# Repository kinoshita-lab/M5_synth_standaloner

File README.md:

# M5 Synth standaloner san

M5 Synth standaloner san is a handy PCB which enables standalone use of:
- Unit Synth https://docs.m5stack.com/ja/unit/Unit-Synth 
- Unit MIDI https://docs.m5stack.com/en/unit/Unit-MIDI

without using a microcontroller such as M5Stack/Stick. 
Both Type A and Type B MIDI IN are supported.

All other product names other than this product are trademarks or registered trademarks of their respective companies.

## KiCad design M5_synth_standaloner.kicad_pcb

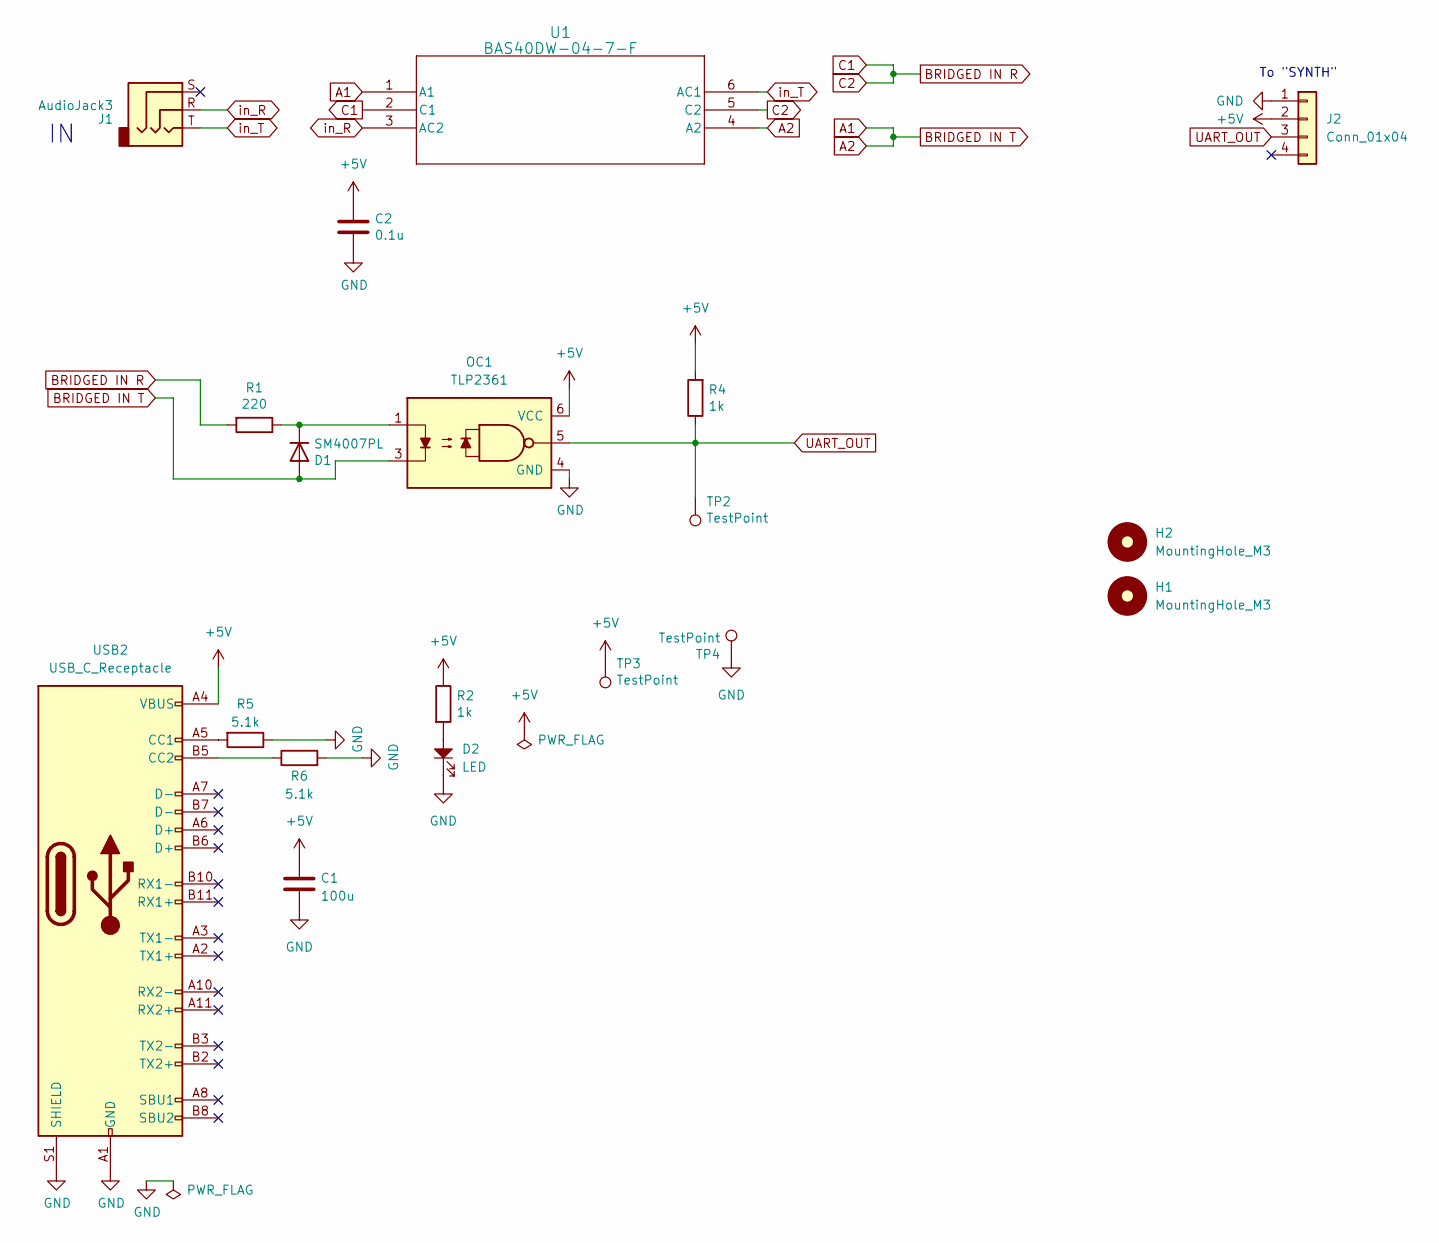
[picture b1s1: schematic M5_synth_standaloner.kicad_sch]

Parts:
C1: 100u; C_1206_3216Metric_Pad1.33x1.80mm_HandSolder; LCSC C15008
C2: 0.1u; C_0402_1005Metric; LCSC C1525
D1: SM4007PL; D_SOD-123; LCSC C64898
D2: LED; LED_0603_1608Metric; LCSC C965808
H1, H2: MountingHole_M3; MountingHole_3.2mm_M3
J1: AudioJack3; 3.5mm_Stereo_TRS_PJ-3210-4A_and_ST-005-G; LCSC C136686
J2: Conn_01x04; SEEEDSTUDIO_114020164; LCSC C604849
OC1: TLP2361; SO-5_4.4x3.6mm_P1.27mm; LCSC C123773
R1: 220; R_1206_3216Metric_Pad1.30x1.75mm_HandSolder; LCSC C17957
R2, R4: 1k; R_0402_1005Metric; LCSC C11702
R5, R6: 5.1k; R_0402_1005Metric; LCSC C25905
TP2, TP3, TP4: TestPoint; TestPoint_THTPad_1.0x1.0mm_Drill0.5mm
U1: BAS40DW-04-7-F; SOT-363_DIO; LCSC C134364
USB2: USB_C_Receptacle; USB_C_Receptacle_HCTL_HC-TYPE-C-16P-01A; LCSC C2894897

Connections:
+5V: C1.1, C2.1, J2.2, OC1.6 (VCC), R2.1, R4.2, TP3.1, USB2.A4 (VBUS), USB2.A9 (VBUS), USB2.B4 (VBUS), USB2.B9 (VBUS)
A1: D1.2 (A), OC1.3, U1.1 (A1), U1.4 (A2)
BRIDGED IN R: R1.2, U1.2 (C1), U1.5 (C2)
GND: C1.2, C2.2, D2.1, J2.1, OC1.4 (GND), R5.1, R6.2, TP4.1, USB2.A1 (GND), USB2.A12 (GND), USB2.B1 (GND), USB2.B12 (GND), USB2.S1 (SHIELD)
unnamed: D1.1 (K), OC1.1, R1.1
unnamed: D2.2, R2.2
unnamed: R5.2, USB2.A5 (CC1)
unnamed: R6.1, USB2.B5 (CC2)
UART_OUT: J2.3, OC1.5, R4.1, TP2.1
in_R: J1.R, U1.3 (AC2)
in_T: J1.T, U1.6 (AC1)

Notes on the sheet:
To "SYNTH"

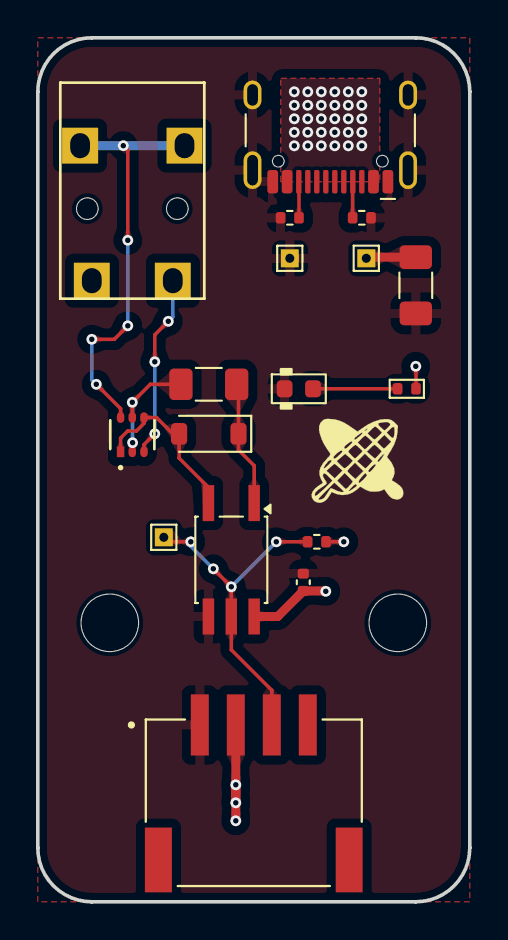
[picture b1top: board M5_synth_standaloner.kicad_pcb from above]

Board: 2 copper layers, 24.0 x 48.0 mm, 19 parts (0 on the bottom side), 11 nets.

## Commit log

2025-04-08 Create LICENSE
